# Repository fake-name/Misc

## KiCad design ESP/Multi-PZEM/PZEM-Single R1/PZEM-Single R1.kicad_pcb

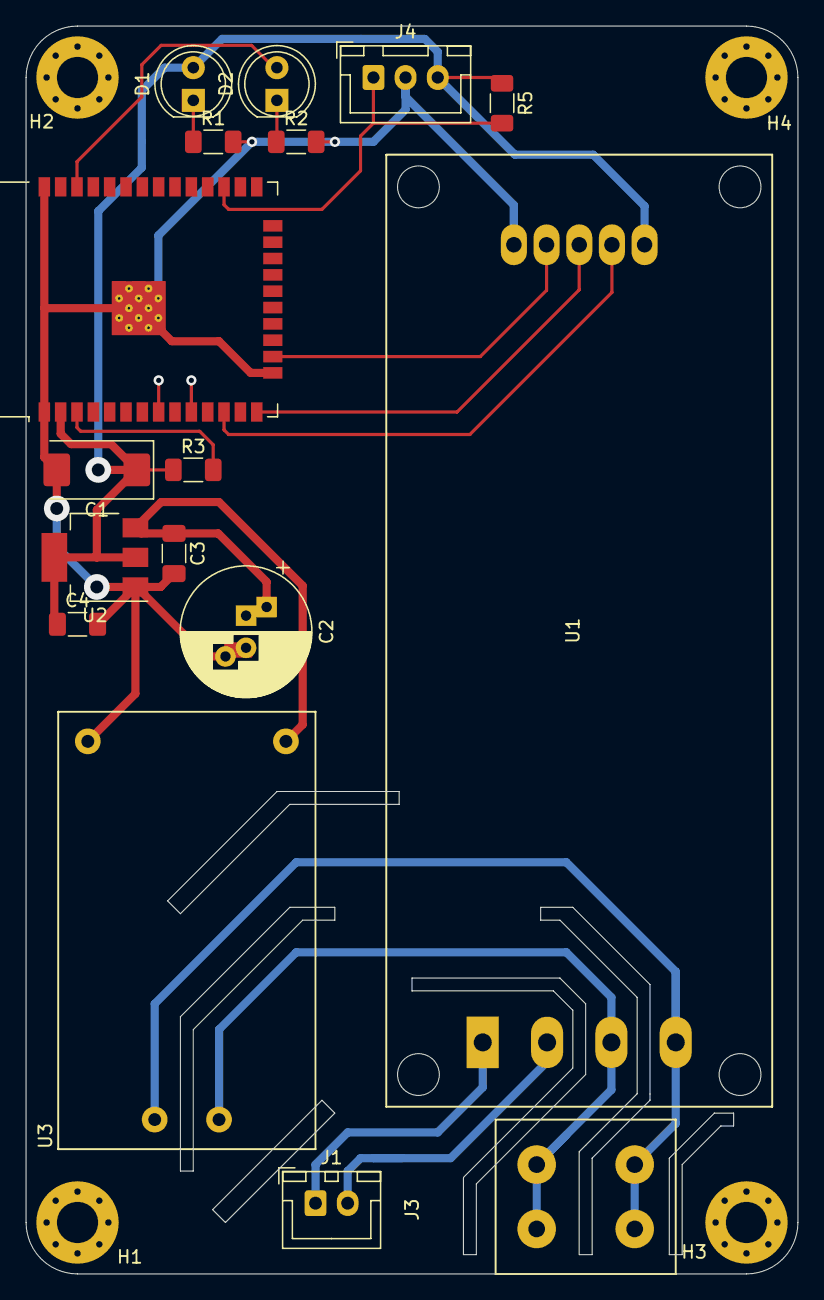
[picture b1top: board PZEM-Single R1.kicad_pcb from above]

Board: 2 copper layers, 60.0 x 97.0 mm, 21 parts (0 on the bottom side), 15 nets.

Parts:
C1: CP; CP_EIA-7343-40_Kemet-Y
C2: CP; CP_Radial_D10.0mm_P2.50mm_P5.00mm
C3, C4: C_Small; C_1206_3216Metric_Pad1.33x1.80mm_HandSolder
D1, D2: LED; LED_D5.0mm
H1, H2, H3, H4: MountingHole; MountingHole_3.2mm_M3_Pad_Via
J1: Conn_01x04; JST_XH_B2B-XH-A_1x02_P2.50mm_Vertical
J3: Conn_01x02; WE 691411410002 - 2 Pin Wire-To-Board Terminal Block
J4: Conn_01x04; JST_XH_B3B-XH-A_1x03_P2.50mm_Vertical
R1, R2, R3, R5: R_Small; R_1206_3216Metric_Pad1.30x1.75mm_HandSolder
U1: PZEM-004T-100A-D-P
U2: AMS1117-3.3; SOT-223-3_TabPin2
U3: HLK-PM01
U4: ESP32-WROOM-32

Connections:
+3V3: C1.1, C4.1, D1.2 (A), J4.3, R3.1, R5.1, U1.5 (VCC), U2.2 (VO), U4.2 (VDD)
+5V: C2.1, C3.1, U2.3 (VI), U3.3 (+Vo)
GND: C1.2, C2.2, C3.2, C4.2, J4.2, R1.2, R2.2, U1.9 (GND), U2.1 (GND), U3.4 (-Vo), U4.1 (GND), U4.15 (GND), U4.38 (GND), U4.39 (GND)
unnamed: D1.1 (K), R1.1
unnamed: D2.2 (A), U4.36 (IO22)
unnamed: D2.1 (K), R2.1
unnamed: J1.1, U1.1 (CT+)
unnamed: J1.2, U1.2 (CT-)
unnamed: J3.1, U1.4 (L), U3.1 (AC)
unnamed: J3.2, U1.3 (N), U3.2 (AC)
unnamed: J4.1, R5.2, U4.27 (IO16)
unnamed: U1.8 (CF), U4.16 (IO13)
unnamed: U1.6 (RX), U4.12 (IO27)
unnamed: U1.7 (TX), U4.14 (IO12)
unnamed: R3.2, U4.3 (EN)

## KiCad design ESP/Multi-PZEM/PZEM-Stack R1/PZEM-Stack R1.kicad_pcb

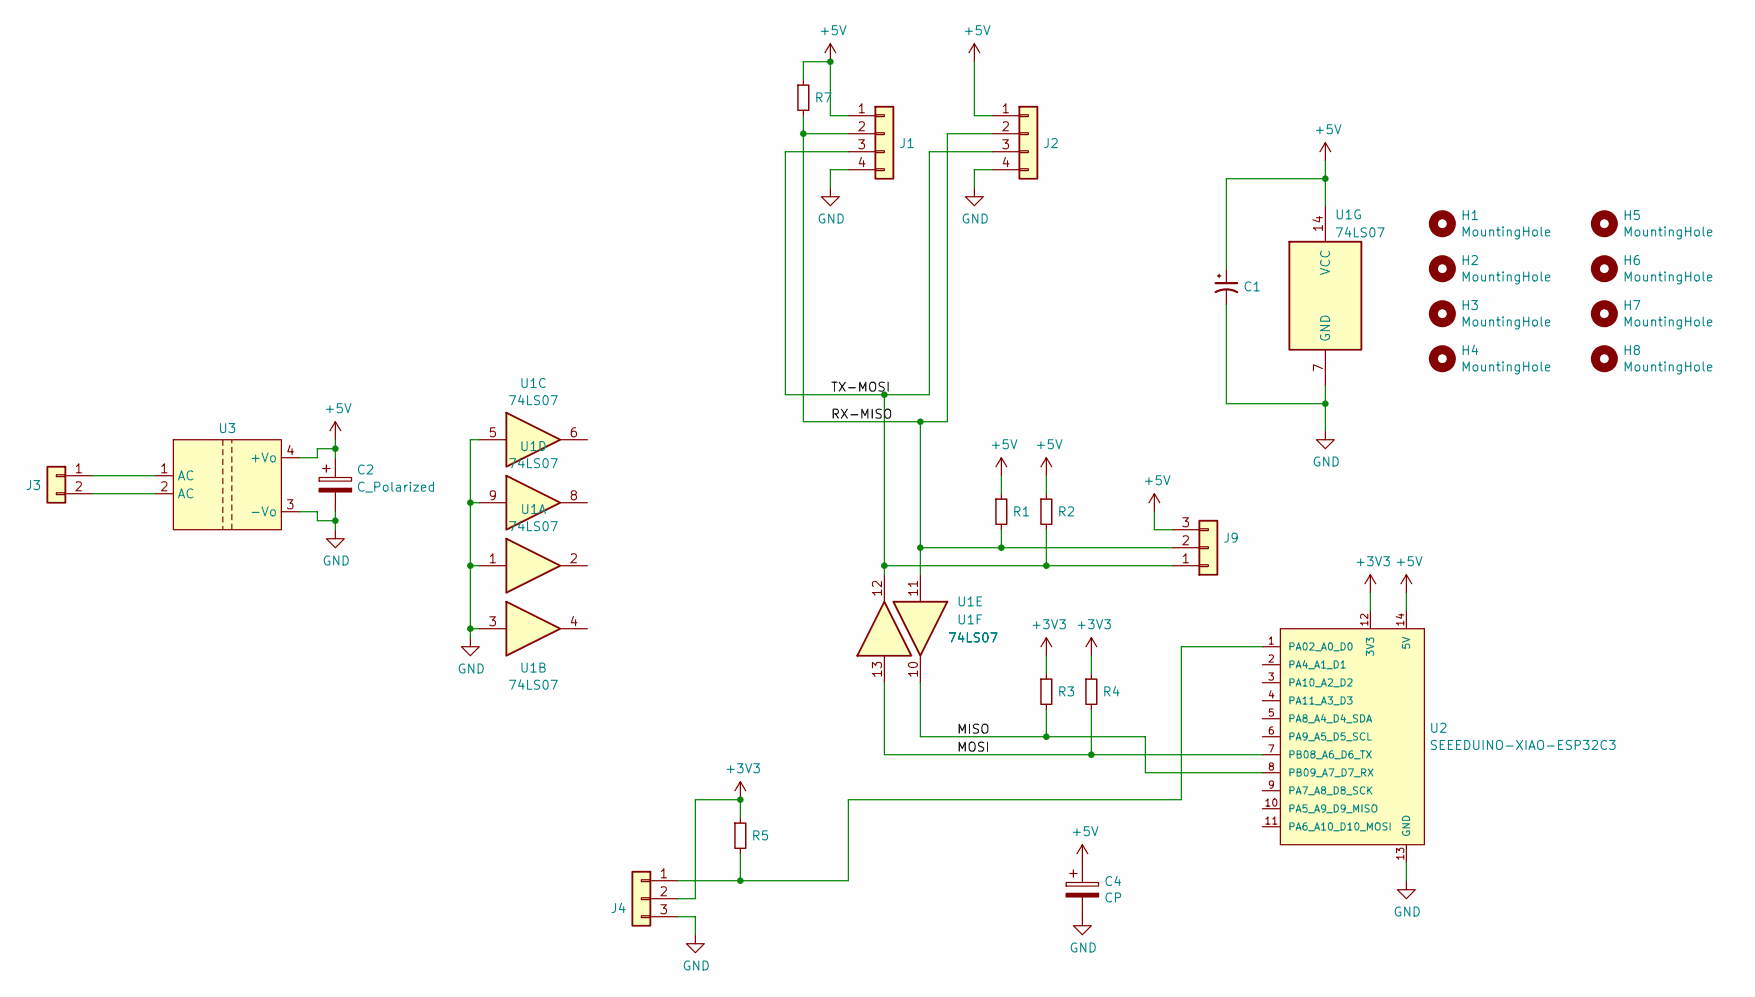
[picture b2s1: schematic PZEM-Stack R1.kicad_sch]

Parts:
C1: CP1_Small; C_Disc_D3.8mm_W2.6mm_P2.50mm
C2: C_Polarized; CP_Radial_D10.0mm_P2.50mm_P5.00mm
C4: CP; CP_Radial_D8.0mm_P2.50mm
H1, H2, H3, H4, H5, H6, H7, H8: MountingHole; MountingHole_3.2mm_M3_Pad_Via
J1, J2: Conn_01x04; JST_XH_B4B-XH-A_1x04_P2.50mm_Vertical
J3: Conn_01x02; WE 691411410002 - 2 Pin Wire-To-Board Terminal Block
J4, J9: Conn_01x04; JST_XH_B3B-XH-A_1x03_P2.50mm_Vertical
R1, R2, R3, R4, R5: R_Small; R_Axial_DIN0207_L6.3mm_D2.5mm_P10.16mm_Horizontal
R7: R_Small; R_1206_3216Metric
U1: 74LS07; DIP-14_W7.62mm_LongPads
U2: SEEEDUINO-XIAO-ESP32C3; MOUDLE14P-SMD-2.54-21X17.8MM
U3: HLK-PM01

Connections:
+3V3: J4.2, R3.1, R4.1, R5.1, U2.12 (3V3)
+5V: C1.1, C2.1, C4.1, J1.1, J2.1, J9.3, R1.1, R2.1, R7.1, U1.14 (VCC), U2.14 (5V), U3.4 (+Vo)
/MISO: R3.2, U1.10, U2.8 (PB09_A7_D7_RX)
/MOSI: R4.2, U1.13, U2.7 (PB08_A6_D6_TX)
/RX-MISO: J1.2, J2.2, J9.2, R1.2, R7.2, U1.11
/TX-MOSI: J1.3, J2.3, J9.1, R2.2, U1.12
GND: C1.2, C2.2, C4.2, J1.4, J2.4, J4.3, U1.1, U1.3, U1.5, U1.7 (GND), U1.9, U2.13 (GND), U3.3 (-Vo)
unnamed: J3.1, U3.1 (AC)
unnamed: J3.2, U3.2 (AC)
unnamed: J4.1, R5.2, U2.1 (PA02_A0_D0)

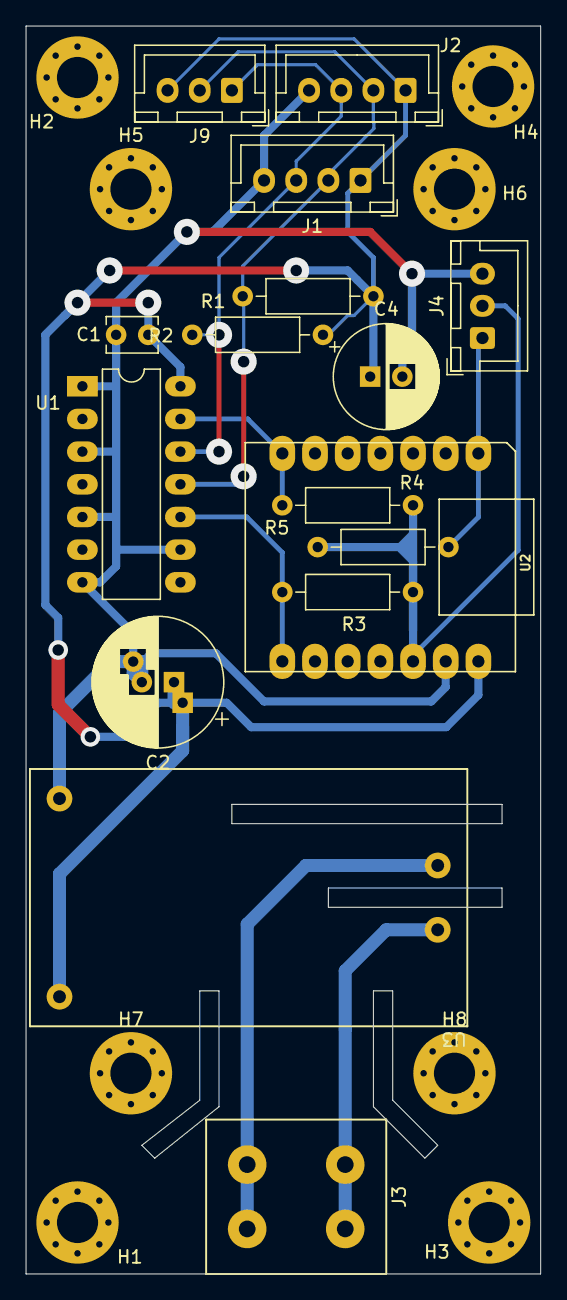
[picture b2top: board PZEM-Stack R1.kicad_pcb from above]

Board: 2 copper layers, 40.0 x 97.0 mm, 25 parts (1 on the bottom side), 10 nets.

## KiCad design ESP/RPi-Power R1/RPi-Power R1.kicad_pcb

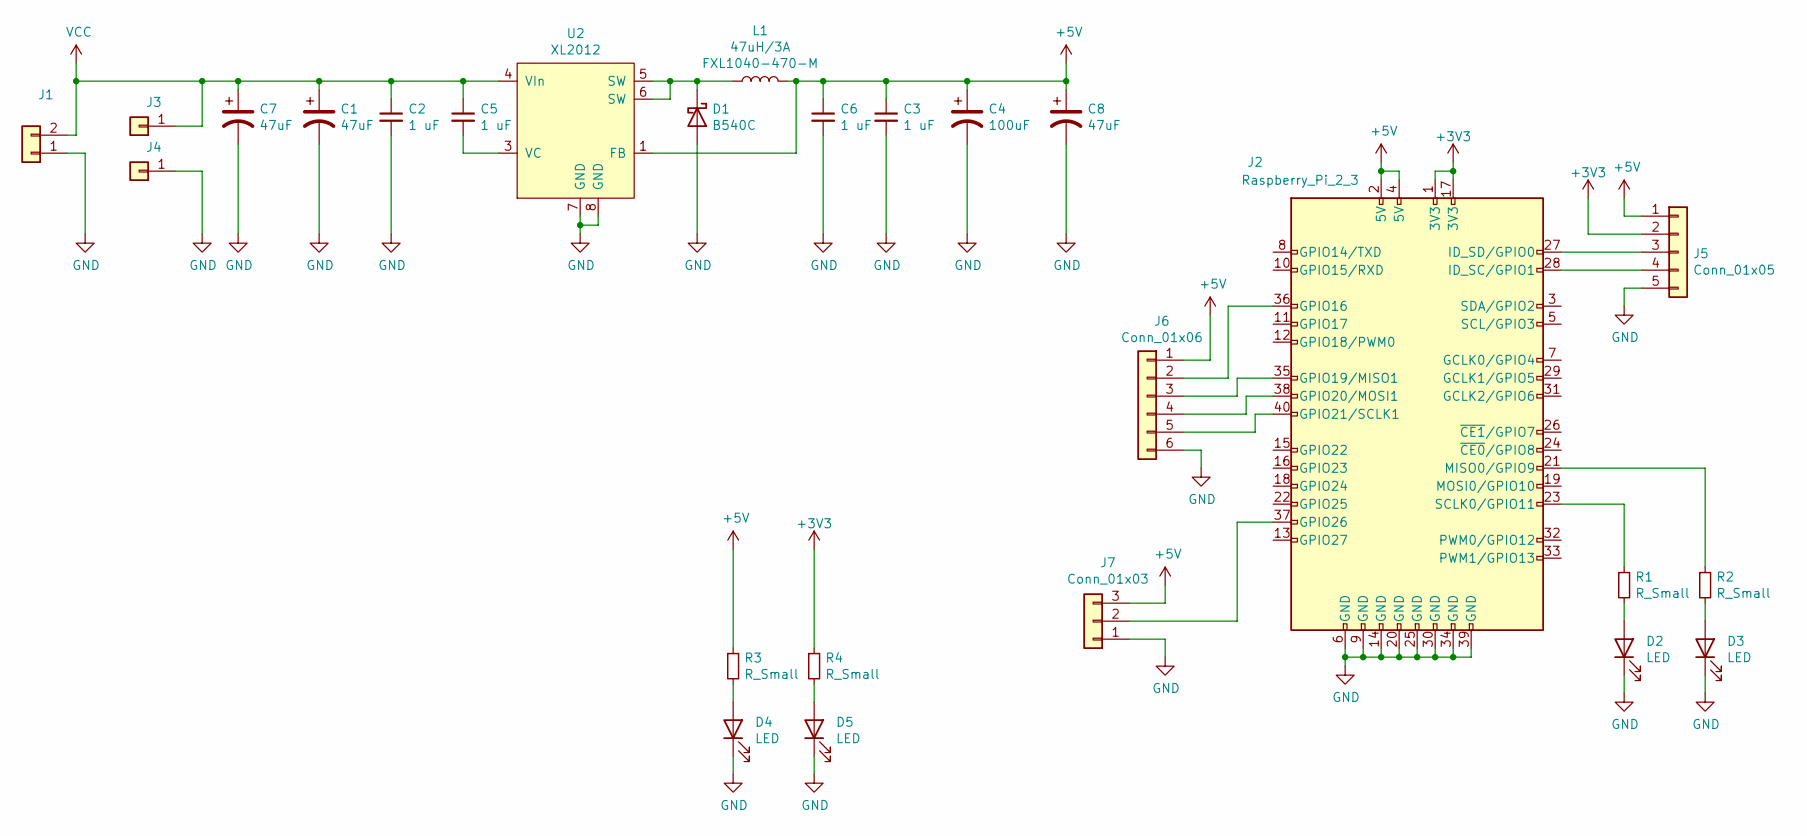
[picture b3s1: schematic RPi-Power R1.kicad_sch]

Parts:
C1, C8: 47uF; CP_Radial_D6.3mm_P2.50mm
C2, C3, C5, C6: 1 uF; C_0603_1608Metric
C4: 100uF; CP_EIA-7343-20_Kemet-V
C7: 47uF; CP_EIA-7343-20_Kemet-V
D1: B540C; D_SMC_Handsoldering
D2, D3, D4, D5: LED; CHIPLED_0603
J1: Conn_01x02; JST_XH_B2B-XH-AM_1x02_P2.50mm_Vertical
J2: Raspberry_Pi_2_3; PinHeader_2x20_P2.54mm_Vertical
J3, J4: Conn_01x01; Pin_D1.3mm_L11.0mm
J5: Conn_01x05; JST_SH_BM05B-SRSS-TB_1x05-1MP_P1.00mm_Vertical
J6: Conn_01x06; JST_SH_BM06B-SRSS-TB_1x06-1MP_P1.00mm_Vertical
J7: Conn_01x03; JST_XH_B3B-XH-AM_1x03_P2.50mm_Vertical
L1: 47uH/3A; L_Wuerth_HCI-1040
R1, R2, R3, R4: R_Small; R_0603_1608Metric
U2: XL2012; SOIC-8_3.9x4.9mm_P1.27mm

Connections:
+3V3: J2.1 (3V3), J2.17 (3V3), J5.2, R4.1
+5V: C3.1, C4.1, C6.1, C8.1, J2.2 (5V), J2.4 (5V), J5.1, J6.1, J7.3, L1.2, R3.1, U2.1 (FB)
GND: C1.2, C2.2, C3.2, C4.2, C6.2, C7.2, C8.2, D1.2 (A), D2.1 (K), D3.1 (K), D4.1 (K), D5.1 (K), J1.1, J2.6 (GND), J2.9 (GND), J2.14 (GND), J2.20 (GND), J2.25 (GND), J2.30 (GND), J2.34 (GND), J2.39 (GND), J4.1, J5.5, J6.6, J7.1, U2.7 (GND), U2.8 (GND)
unnamed: C5.2, U2.3 (VC)
unnamed: D1.1 (K), L1.1, U2.5 (SW), U2.6 (SW)
unnamed: D2.2 (A), R1.2
unnamed: D3.2 (A), R2.2
unnamed: D4.2 (A), R3.2
unnamed: D5.2 (A), R4.2
unnamed: J2.21 (MISO0/GPIO9), R2.1
unnamed: J2.23 (SCLK0/GPIO11), R1.1
unnamed: J2.27 (ID_SD/GPIO0), J5.3
unnamed: J2.28 (ID_SC/GPIO1), J5.4
unnamed: J2.35 (GPIO19/MISO1), J6.3
unnamed: J2.36 (GPIO16), J6.2
unnamed: J2.37 (GPIO26), J7.2
unnamed: J2.38 (GPIO20/MOSI1), J6.4
unnamed: J2.40 (GPIO21/SCLK1), J6.5
VCC: C1.1, C2.1, C5.1, C7.1, J1.2, J3.1, U2.4 (VIn)

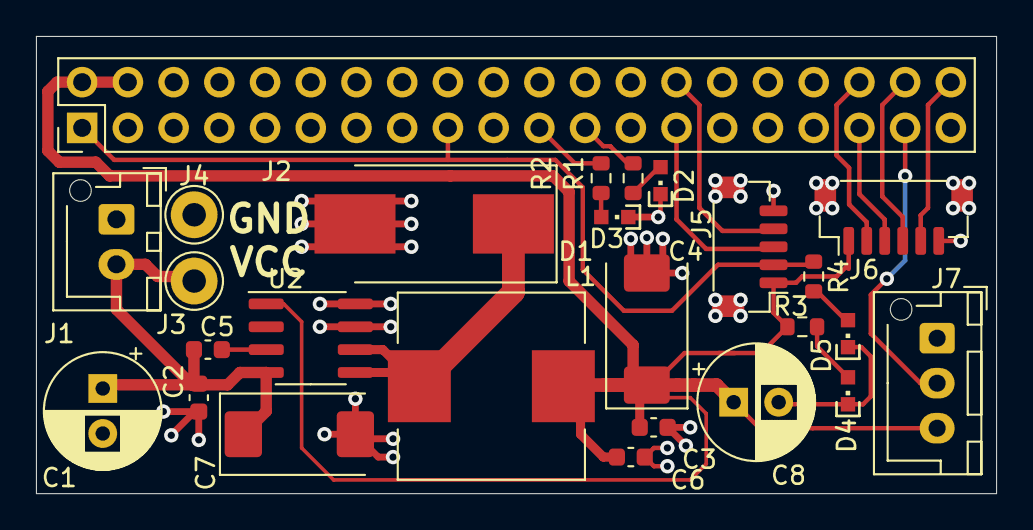
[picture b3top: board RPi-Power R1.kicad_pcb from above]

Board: 2 copper layers, 53.3 x 25.4 mm, 26 parts (0 on the bottom side), 19 nets.

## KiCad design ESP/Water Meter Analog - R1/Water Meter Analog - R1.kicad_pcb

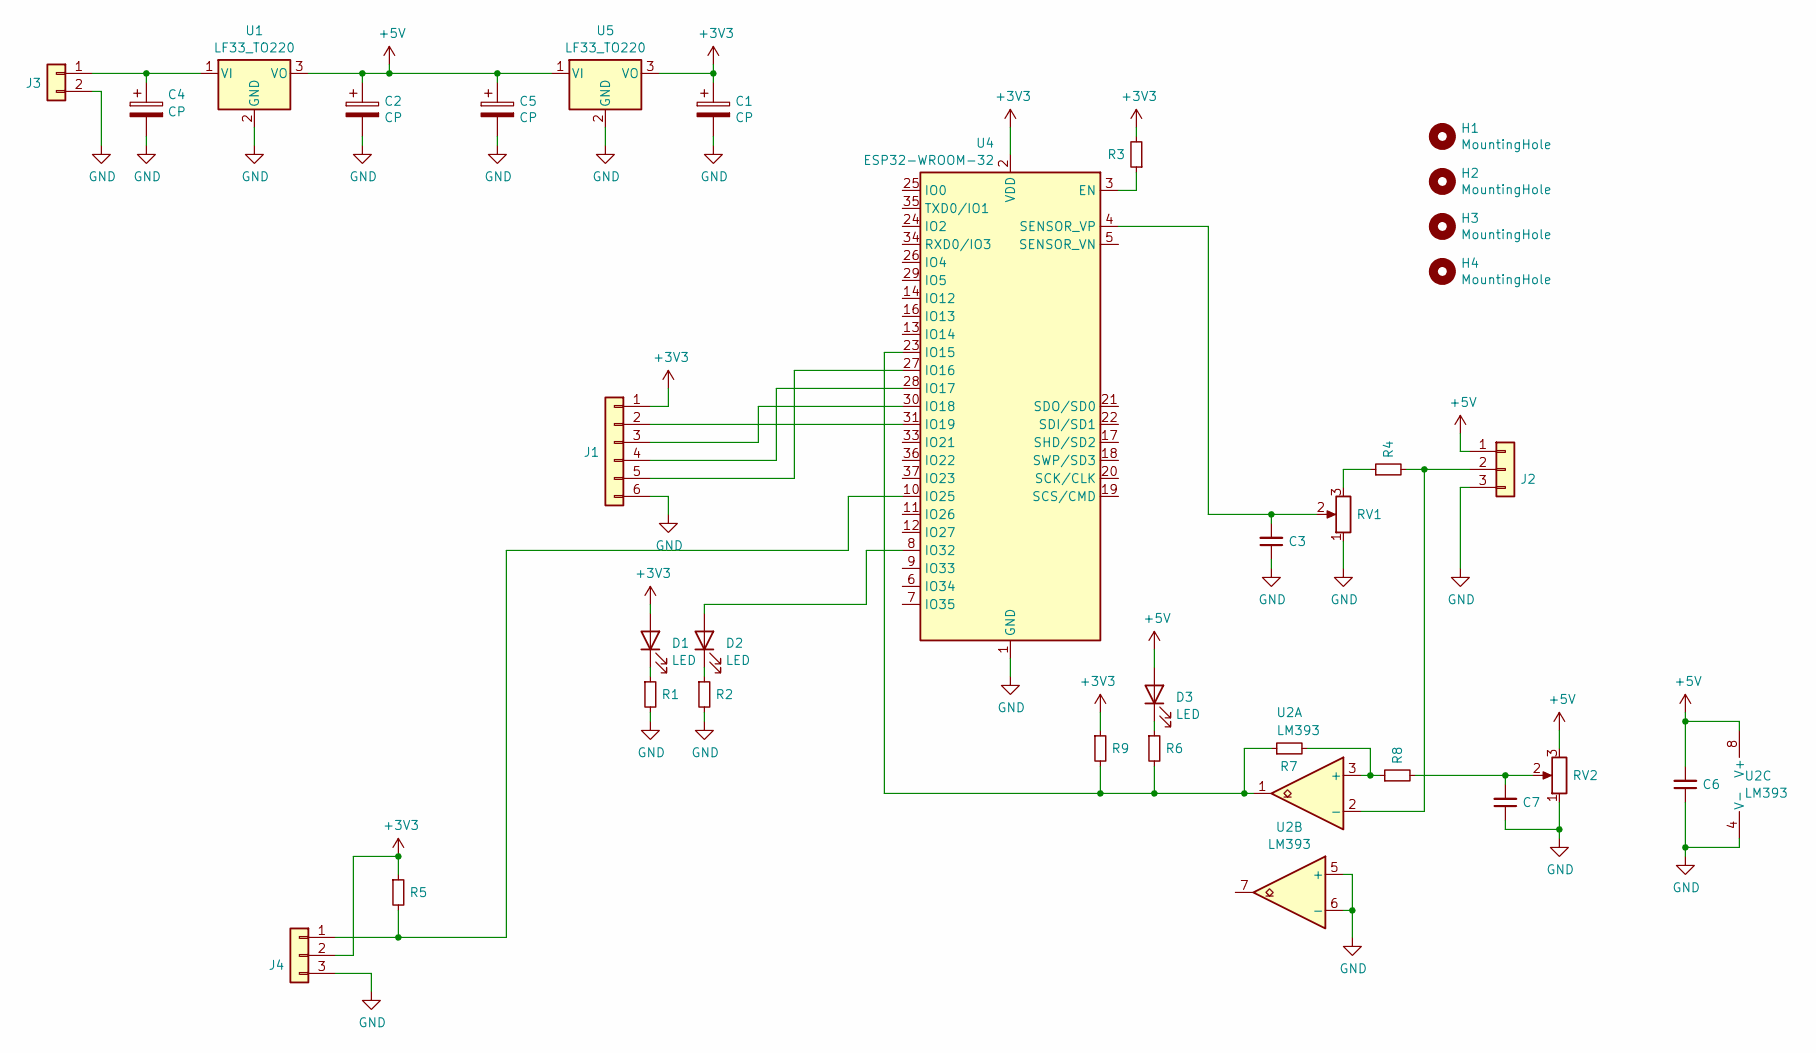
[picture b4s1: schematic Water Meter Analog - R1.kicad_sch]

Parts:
C1, C2, C5: CP; CP_Radial_D8.0mm_P2.50mm
C3, C6, C7: C_Small; C_1206_3216Metric_Pad1.33x1.80mm_HandSolder
C4: CP; CP_Radial_D10.0mm_P2.50mm_P5.00mm
D1, D2, D3: LED; LED_D5.0mm
H1, H2, H3, H4: MountingHole; MountingHole_3.2mm_M3_Pad_Via
J1: Conn_01x04; JST_XH_B6B-XH-A_1x06_P2.50mm_Vertical
J2, J4: Conn_01x04; JST_XH_B3B-XH-A_1x03_P2.50mm_Vertical
J3: Conn_01x02; WE 691411410002 - 2 Pin Wire-To-Board Terminal Block
R1, R2, R4, R5, R6, R7, R8: R_Small; R_Axial_DIN0207_L6.3mm_D2.5mm_P10.16mm_Horizontal
R3, R9: R_Small; R_Axial_DIN0309_L9.0mm_D3.2mm_P2.54mm_Vertical
RV1, RV2: R_Potentiometer; Potentiometer_Bourns_3299Y_Vertical
U1, U5: LF33_TO220; TO-220-3_Vertical
U2: LM393; SO-8_5.3x6.2mm_P1.27mm
U4: ESP32-WROOM-32

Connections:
+3V3: C1.1, D1.2 (A), J1.1, J4.2, R3.2, R5.1, R9.1, U4.2 (VDD), U5.3 (VO)
+5V: C2.1, C5.1, C6.2, D3.2 (A), J2.1, RV2.3, U1.3 (VO), U2.8 (V+), U5.1 (VI)
GND: C1.2, C2.2, C3.1, C4.2, C5.2, C6.1, C7.1, J1.6, J2.3, J3.2, J4.3, R1.2, R2.2, RV1.1, RV2.1, U1.2 (GND), U2.4 (V-), U2.5 (+), U2.6 (-), U4.1 (GND), U4.15 (GND), U4.38 (GND), U4.39 (GND), U5.2 (GND)
unnamed: C7.2, R8.2, RV2.2
unnamed: D1.1 (K), R1.1
unnamed: D2.2 (A), U4.8 (IO32)
unnamed: D2.1 (K), R2.1
unnamed: D3.1 (K), R6.1
unnamed: J1.2, U4.31 (IO19)
unnamed: J1.3, U4.30 (IO18)
unnamed: J1.4, U4.28 (IO17)
unnamed: J1.5, U4.27 (IO16)
unnamed: J2.2, R4.2, U2.2 (-)
unnamed: C4.1, J3.1, U1.1 (VI)
unnamed: J4.1, R5.2, U4.10 (IO25)
unnamed: R4.1, RV1.3
unnamed: R7.2, R8.1, U2.3 (+)
unnamed: R3.1, U4.3 (EN)
unnamed: R6.2, R7.1, R9.2, U2.1, U4.23 (IO15)
unnamed: C3.2, RV1.2, U4.4 (SENSOR_VP)

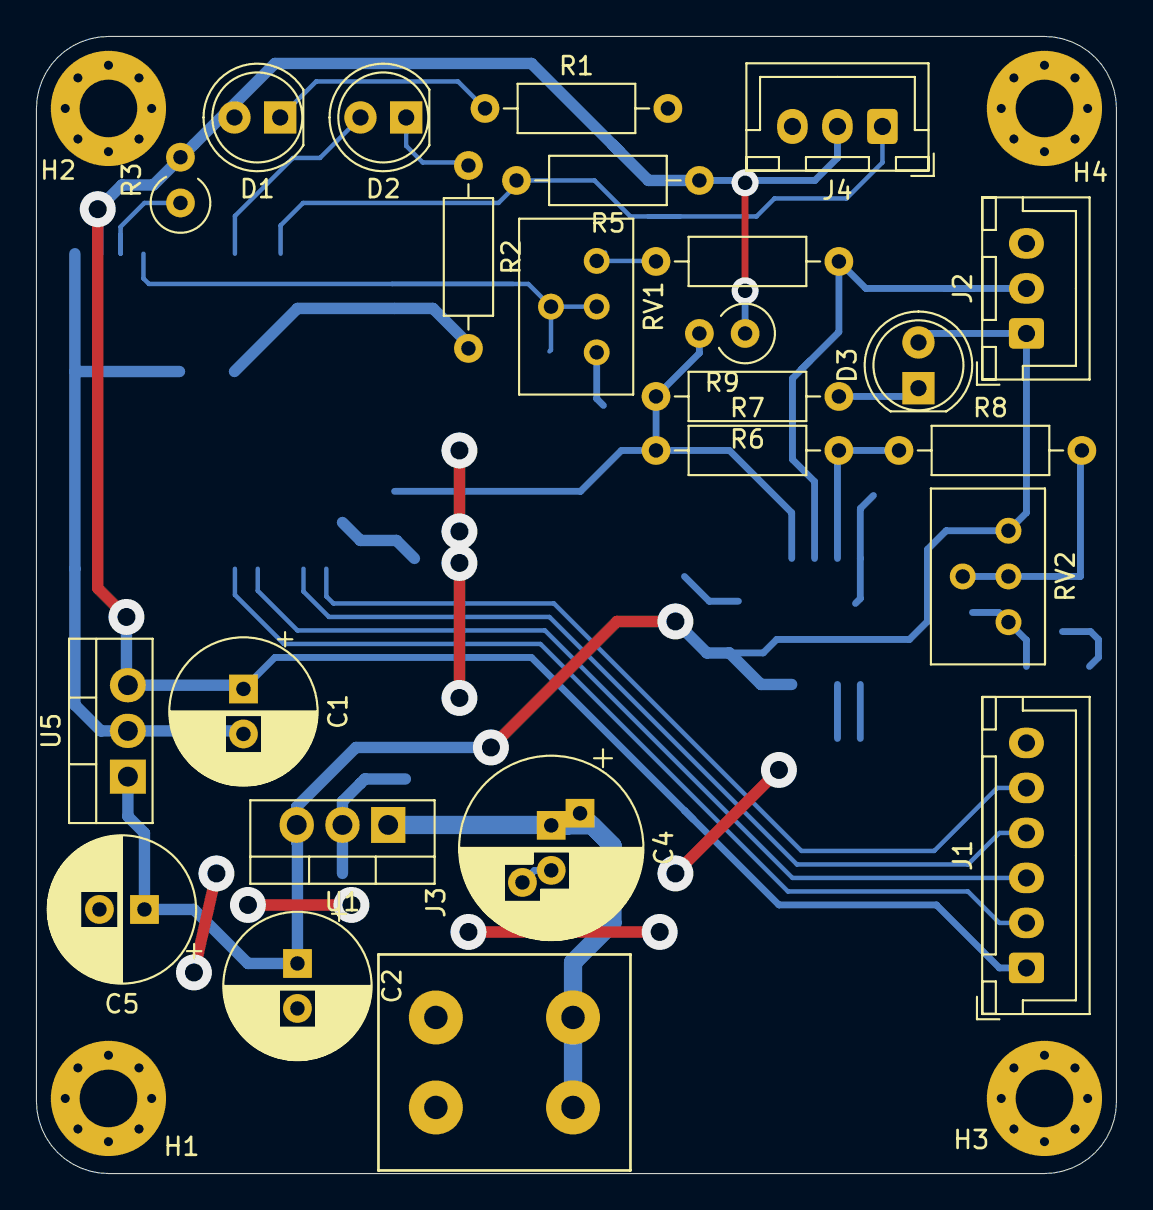
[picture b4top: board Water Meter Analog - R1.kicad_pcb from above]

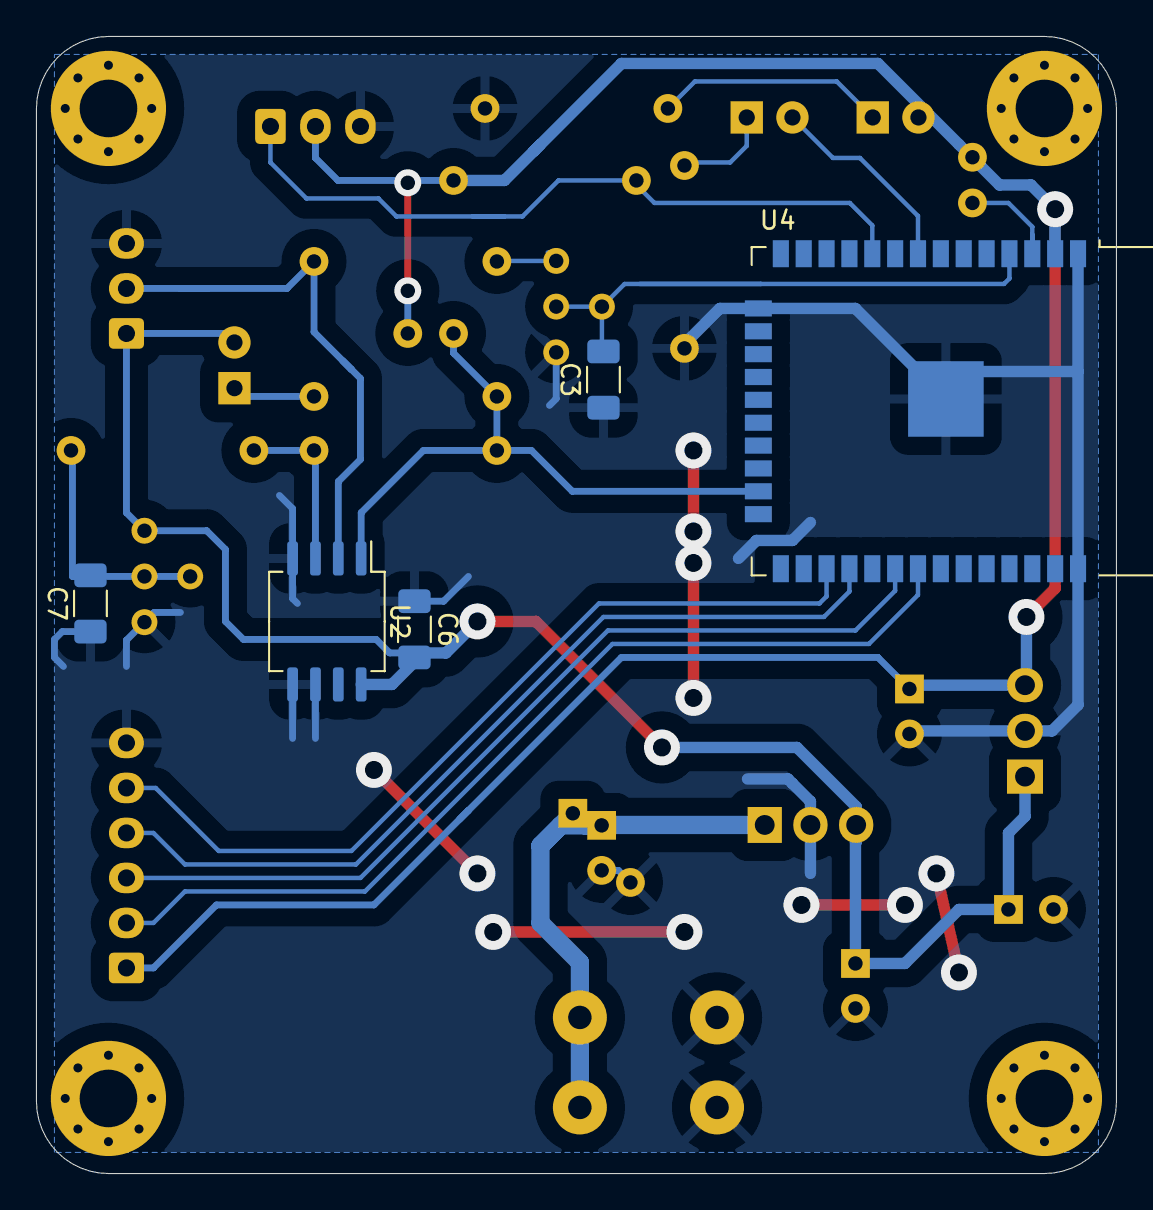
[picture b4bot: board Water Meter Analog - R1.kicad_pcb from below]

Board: 2 copper layers, 60.0 x 63.2 mm, 33 parts (5 on the bottom side), 20 nets.

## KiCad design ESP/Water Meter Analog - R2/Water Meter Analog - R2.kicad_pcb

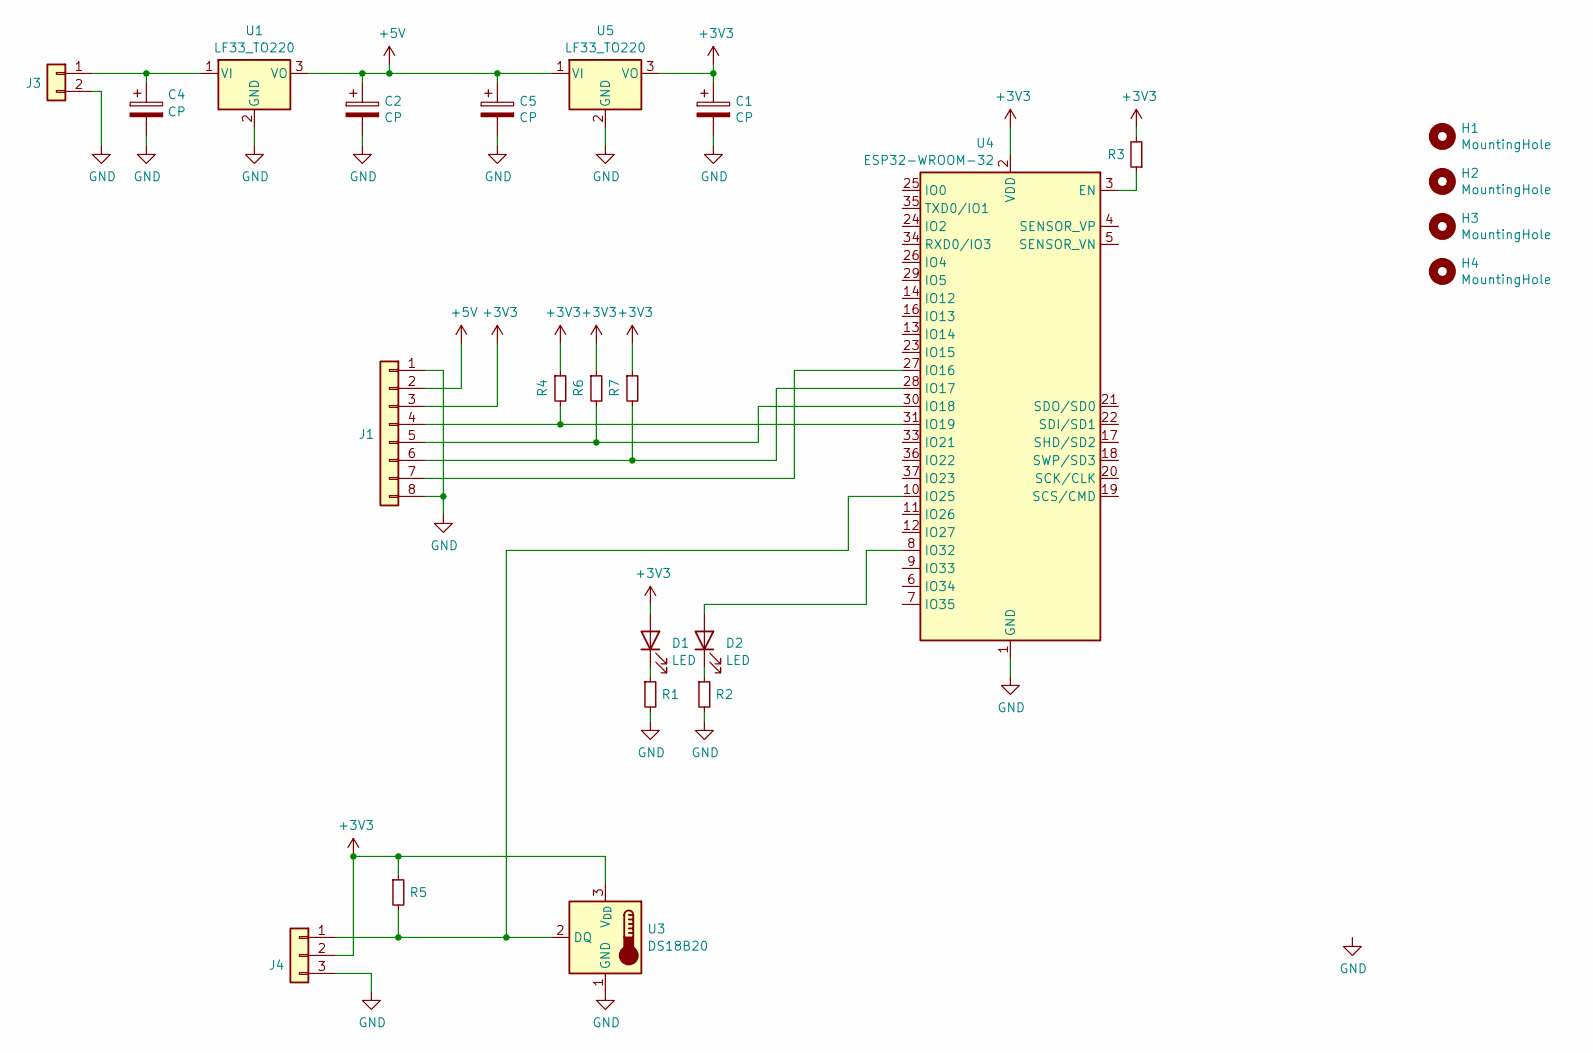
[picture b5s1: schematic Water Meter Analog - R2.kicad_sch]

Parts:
C1, C2, C5: CP; CP_Radial_D8.0mm_P2.50mm
C4: CP; CP_Radial_D10.0mm_P2.50mm_P5.00mm
D1, D2: LED; LED_D5.0mm
H1, H2, H3, H4: MountingHole; MountingHole_3.2mm_M3_Pad_Via
J1: Conn_01x04; JST_XH_B8B-XH-A_1x08_P2.50mm_Vertical
J3: Conn_01x02; WE 691411410002 - 2 Pin Wire-To-Board Terminal Block
J4: Conn_01x04; JST_XH_B3B-XH-A_1x03_P2.50mm_Vertical
R1, R2, R4, R5, R6, R7: R_Small; R_Axial_DIN0207_L6.3mm_D2.5mm_P10.16mm_Horizontal
R3: R_Small; R_Axial_DIN0309_L9.0mm_D3.2mm_P2.54mm_Vertical
U1, U5: LF33_TO220; TO-220-3_Vertical
U3: DS18B20; TO-92_Inline_Wide
U4: ESP32-WROOM-32

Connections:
+3V3: C1.1, D1.2 (A), J1.3, J4.2, R3.2, R4.1, R5.1, R6.1, R7.1, U3.3 (V_{DD}), U4.2 (VDD), U5.3 (VO)
+5V: C2.1, C5.1, J1.2, U1.3 (VO), U5.1 (VI)
GND: C1.2, C2.2, C4.2, C5.2, J1.1, J1.8, J3.2, J4.3, R1.2, R2.2, U1.2 (GND), U3.1 (GND), U4.1 (GND), U4.15 (GND), U4.38 (GND), U4.39 (GND), U5.2 (GND)
unnamed: D1.1 (K), R1.1
unnamed: D2.2 (A), U4.8 (IO32)
unnamed: D2.1 (K), R2.1
unnamed: J1.4, R4.2, U4.31 (IO19)
unnamed: J1.5, R6.2, U4.30 (IO18)
unnamed: J1.6, R7.2, U4.28 (IO17)
unnamed: J1.7, U4.27 (IO16)
unnamed: C4.1, J3.1, U1.1 (VI)
unnamed: J4.1, R5.2, U3.2 (DQ), U4.10 (IO25)
unnamed: R3.1, U4.3 (EN)

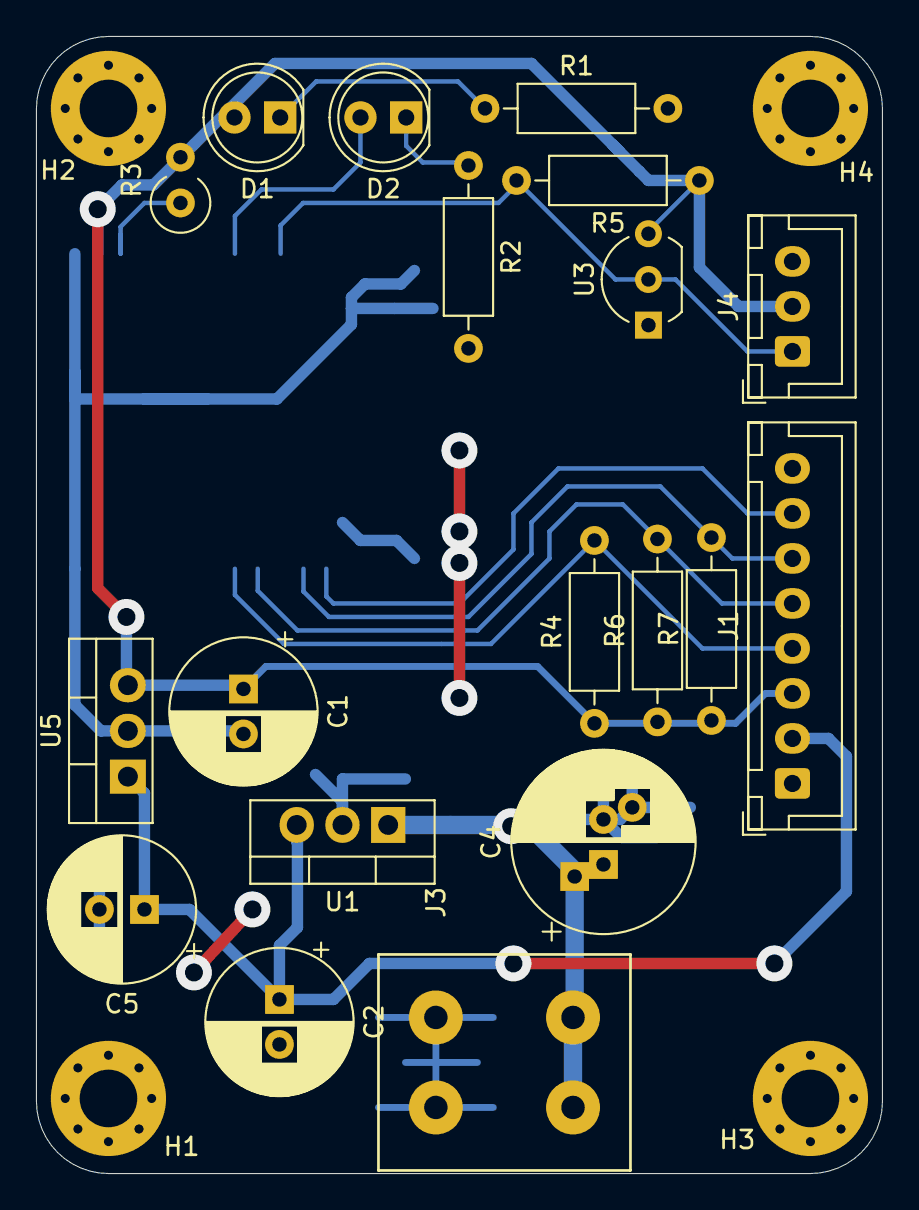
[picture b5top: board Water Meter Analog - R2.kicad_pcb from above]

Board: 2 copper layers, 47.0 x 63.2 mm, 24 parts (1 on the bottom side), 13 nets.

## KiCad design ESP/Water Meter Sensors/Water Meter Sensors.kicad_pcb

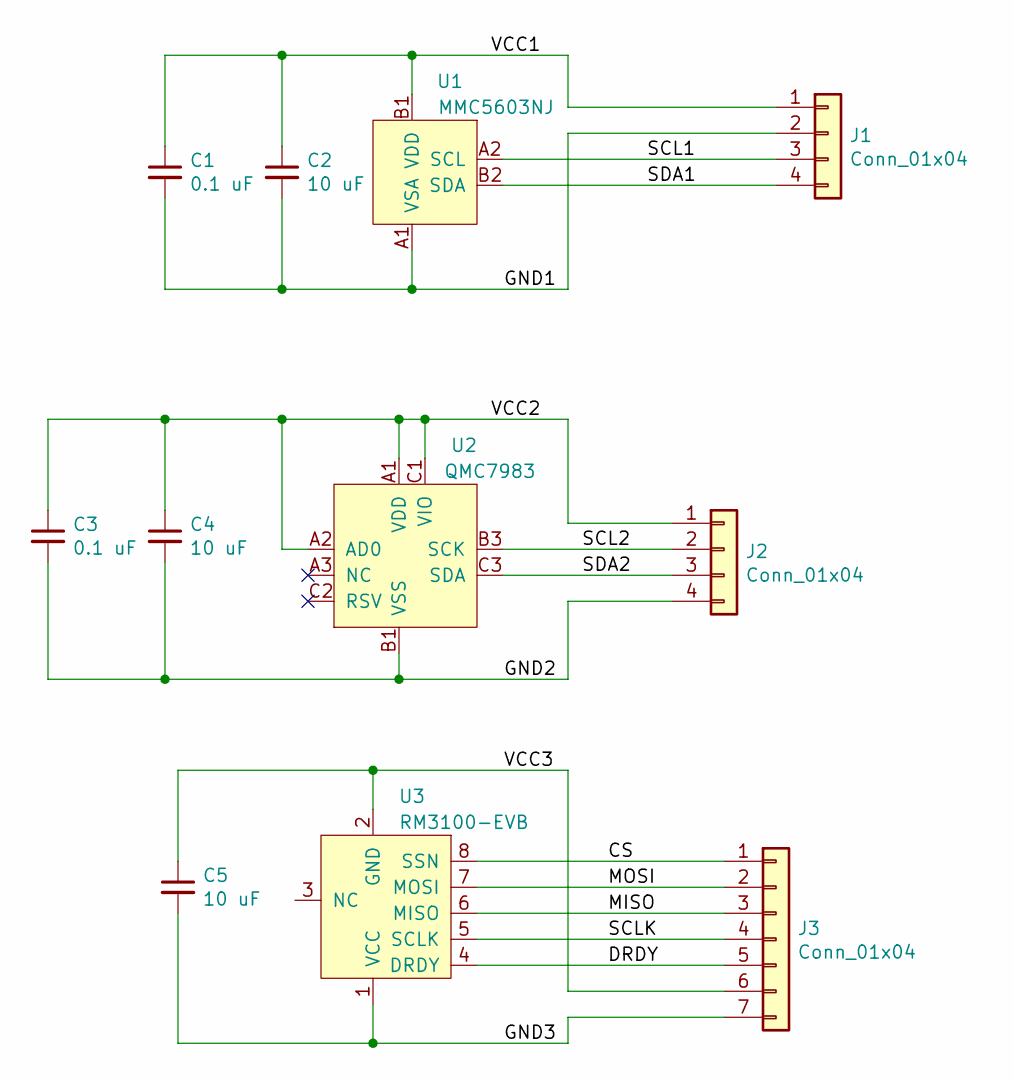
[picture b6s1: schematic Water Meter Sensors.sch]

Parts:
C1, C3: 0.1 uF; C_0603_1608Metric_Pad1.05x0.95mm_HandSolder
C2, C4, C5: 10 uF; C_0603_1608Metric_Pad1.05x0.95mm_HandSolder
J1, J2: Conn_01x04; JST_PH_B4B-PH-SM4-TB_1x04-1MP_P2.00mm_Vertical
J3: Conn_01x04; JST_PH_B7B-PH-SM4-TB_1x07-1MP_P2.00mm_Vertical
U1: MMC5603NJ; WLP-4-0.4mm_pitch-0.82mm_sq
U2: QMC7983; WLCSP-8_3x3_1.2x1.2mm
U3: RM3100-EVB

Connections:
/CS: J3.1, U3.8 (SSN)
/DRDY: J3.5, U3.4 (DRDY)
/GND1: C1.2, C2.2, J1.2, U1.A1 (VSA)
/GND2: C3.2, C4.2, J2.4, U2.B1 (VSS)
/GND3: C5.2, J3.7, U3.1 (VCC)
/MISO: J3.3, U3.6 (MISO)
/MOSI: J3.2, U3.7 (MOSI)
/SCL1: J1.3, U1.A2 (SCL)
/SCL2: J2.2, U2.B3 (SCK)
/SCLK: J3.4, U3.5 (SCLK)
/SDA1: J1.4, U1.B2 (SDA)
/SDA2: J2.3, U2.C3 (SDA)
/VCC1: C1.1, C2.1, J1.1, U1.B1 (VDD)
/VCC2: C3.1, C4.1, J2.1, U2.A1 (VDD), U2.A2 (AD0), U2.C1 (VIO)
/VCC3: C5.1, J3.6, U3.2 (GND)

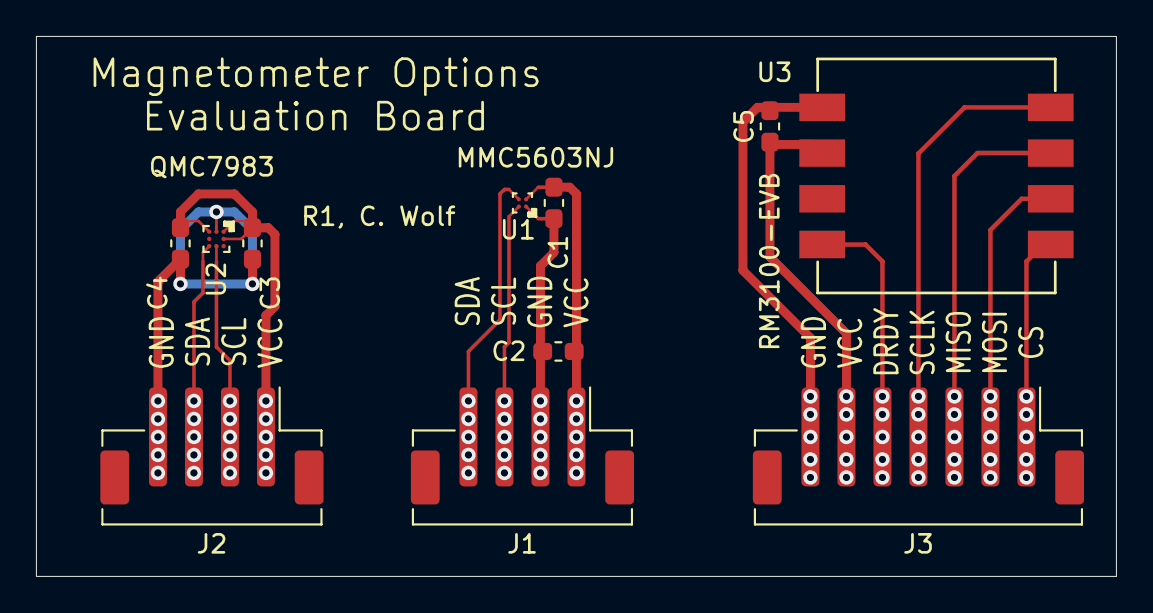
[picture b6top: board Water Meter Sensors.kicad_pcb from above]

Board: 2 copper layers, 60.0 x 30.0 mm, 11 parts (0 on the bottom side), 15 nets.
